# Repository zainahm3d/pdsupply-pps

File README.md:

# pdsupply-pps
single channel USB PD PPS capable power supply

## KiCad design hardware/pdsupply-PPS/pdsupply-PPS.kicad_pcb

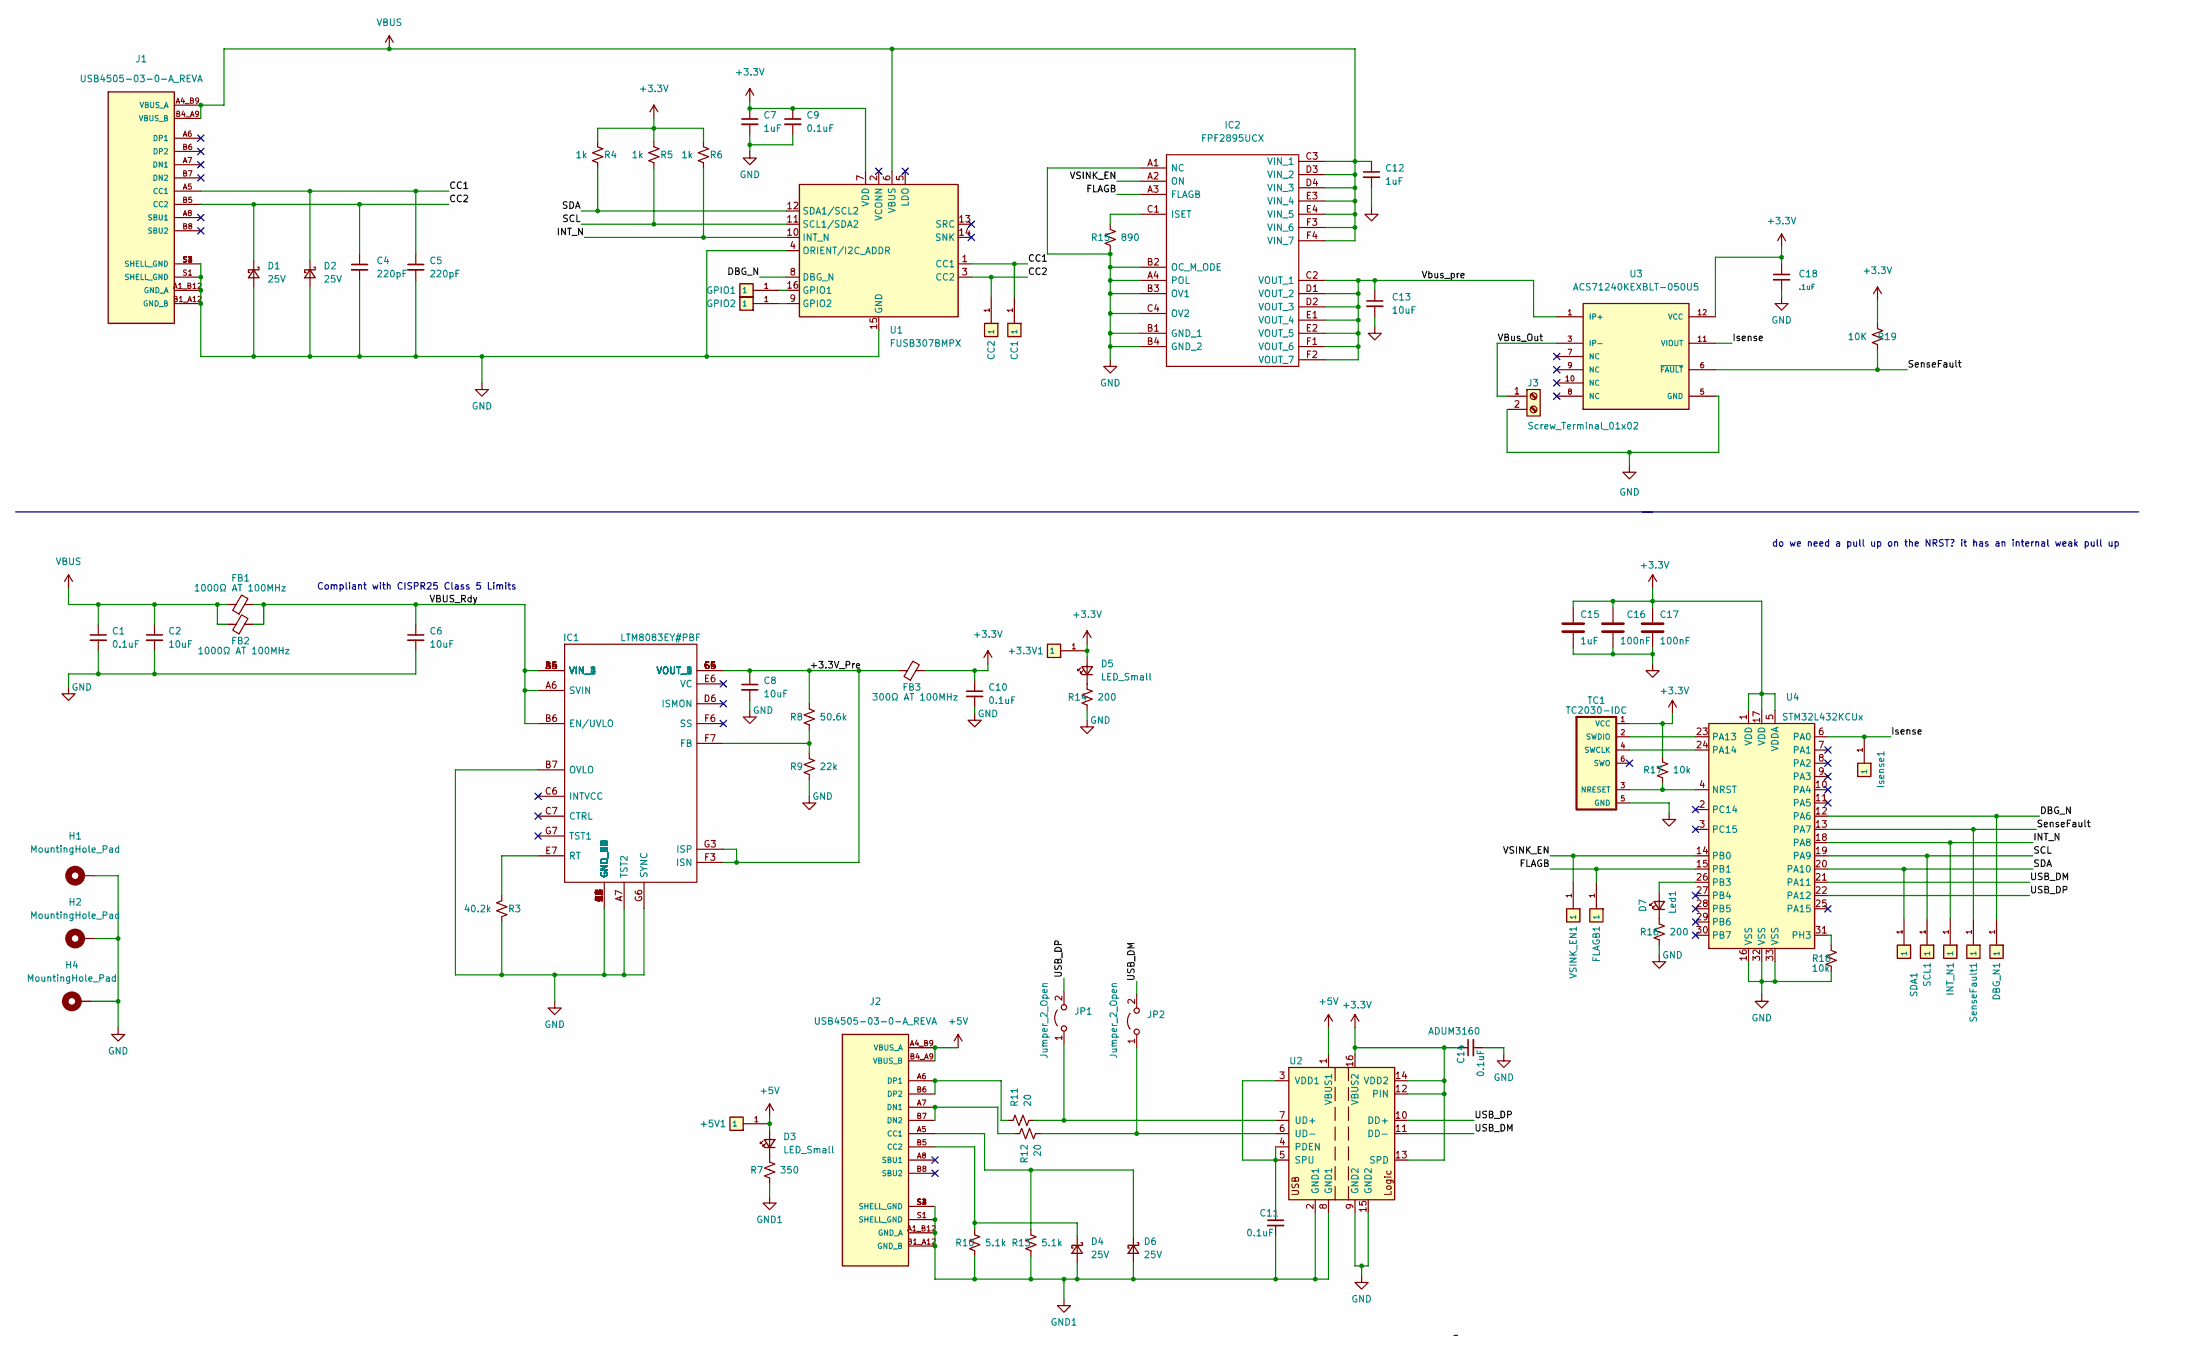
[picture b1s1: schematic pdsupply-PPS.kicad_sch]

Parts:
+3.3V1, +5V1: RCU-0C; TP+195X110; PARTREV BA1
C1, C9, C11, C14: 0.1uF; C_0603_1608Metric
C2, C6: 10uF; C_1206_3216Metric
C4, C5: 220pF; C_0603_1608Metric
C7, C12, C15: 1uF; C_0603_1608Metric
C8: 10uF; C_1210_3225Metric
C10: 0.1uF; C_0805_2012Metric
C13: 10uF; C_0603_1608Metric
C16, C17: 100nF; C_0603_1608Metric
C18: .1uF; C_0603_1608Metric
CC1, CC2: RCU-0C; TP+195X110; PARTREV BA1
D1, D2, D4, D6: 25V; D_0603_1608Metric
D3, D5: LED_Small; LED_0603_1608Metric
D7: Led1; LED_0603_1608Metric
DBG_N1: RCU-0C; TP+195X110; PARTREV BA1
FB1, FB2: 1000Ω AT 100MHz; L_0805_2012Metric
FB3: 300Ω AT 100MHz; L_0805_2012Metric
FLAGB1: RCU-0C; TP+195X110; PARTREV BA1
GPIO1, GPIO2: RCU-0C; TP+195X110; PARTREV BA1
H1, H2, H4: MountingHole_Pad; MountingHole_3mm_Pad
IC1: LTM8083EY#PBF; BGA49C80P7X7_625X625X242; Manufacturer_Part_Number LTM8083EY#PBF; Mouser Part Number 584-LTM8083EY#PBF
IC2: FPF2895UCX; BGA24C40P4X6_167X260X61; Manufacturer_Part_Number FPF2895UCX; Mouser Part Number 512-FPF2895UCX
INT_N1: RCU-0C; TP+195X110; PARTREV BA1
Isense1: RCU-0C; TP+195X110; PARTREV BA1
J1, J2: USB4505-03-0-A_REVA; GCT_USB4505-03-0-A_REVA; PARTREV A
J3: Screw_Terminal_01x02; TerminalBlock_Phoenix_MKDS-1,5-2_1x02_P5.00mm_Horizontal
JP1, JP2: Jumper_2_Open; SolderJumper-2_P1.3mm_Open_TrianglePad1.0x1.5mm
R3: 40.2k; R_0603_1608Metric
R4, R5, R6: 1k; R_0603_1608Metric
R7: 350; R_0603_1608Metric
R8: 50.6k; R_0603_1608Metric
R9: 22k; R_0603_1608Metric
R10, R13: 5.1k; R_0603_1608Metric
R11, R12: 20; R_0603_1608Metric
R14, R16: 200; R_0603_1608Metric
R15: 890; R_0603_1608Metric
R17, R18: 10k; R_0603_1608Metric
R19: 10K; R_0603_1608Metric
SCL1: RCU-0C; TP+195X110; PARTREV BA1
SDA1: RCU-0C; TP+195X110; PARTREV BA1
SenseFault1: RCU-0C; TP+195X110; PARTREV BA1
TC1: TC2030-IDC
U1: FUSB307BMPX; WQFN-16-1EP_3x3mm_P0.5mm_EP1.75x1.75mm
U2: ADUM3160; SOIC-16W_7.5x10.3mm_P1.27mm
U3: ACS71240KEXBLT-050U5; XDCR_ACS71240KEXBLT-050U5; PARTREV 3
U4: STM32L432KCUx; QFN-32-1EP_5x5mm_P0.5mm_EP3.45x3.45mm
VSINK_EN1: RCU-0C; TP+195X110; PARTREV BA1

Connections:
+3V3: +3.3V1.1, C7.1, C9.1, C10.1, C14.1, C15.1, C16.1, C17.1, C18.1, D5.2 (A), FB3.2, R4.2, R5.2, R6.2, R17.1, R19.2, TC1.1 (VCC), U1.7 (VDD), U2.12 (PIN), U2.13 (SPD), U2.14 (VDD2), U2.16 (VBUS2), U3.12 (VCC), U4.1 (VDD), U4.5 (VDDA), U4.17 (VDD)
+5V: +5V1.1, D3.2 (A), J2.A4_B9 (VBUS_A), J2.B4_A9 (VBUS_B), U2.1 (VBUS1)
/+3.3V_Pre: C8.1, FB3.1, IC1.F3 (ISN), IC1.F4 (VOUT_1), IC1.F5 (VOUT_2), IC1.G3 (ISP), IC1.G4 (VOUT_3), IC1.G5 (VOUT_4), R8.1
/CC1: C5.1, CC1.1, D2.1 (K), J1.A5 (CC1), U1.1 (CC1)
/CC2: C4.1, CC2.1, D1.1 (K), J1.B5 (CC2), U1.3 (CC2)
/DBG_N: DBG_N1.1, U1.8 (DBG_N), U4.12 (PA6)
/FLAGB: FLAGB1.1, IC2.A3 (FLAGB), U4.15 (PB1)
/INT_N: INT_N1.1, R6.1, U1.10 (INT_N), U4.18 (PA8)
/Isense: Isense1.1, U3.11 (VIOUT), U4.6 (PA0)
/SCL: R5.1, SCL1.1, U1.11 (SCL1/SDA2), U4.19 (PA9)
/SDA: R4.1, SDA1.1, U1.12 (SDA1/SCL2), U4.20 (PA10)
/SenseFault: R19.1, SenseFault1.1, U3.6 (~FAULT), U4.13 (PA7)
/USB_DM: JP2.2 (B), U2.11 (DD-), U4.21 (PA11)
/USB_DP: JP1.2 (B), U2.10 (DD+), U4.22 (PA12)
/VBUS_Rdy: C6.1, FB1.2, FB2.2, IC1.A4 (VIN_1), IC1.A5 (VIN_2), IC1.A6 (SVIN), IC1.B4 (VIN_3), IC1.B5 (VIN_4), IC1.B6 (EN/UVLO)
/VBus_Out: J3.1, U3.3 (IP-)
/VSINK_EN: IC2.A2 (ON), U4.14 (PB0), VSINK_EN1.1
/Vbus_pre: C13.1, IC2.C2 (VOUT_1), IC2.D1 (VOUT_2), IC2.D2 (VOUT_3), IC2.E1 (VOUT_4), IC2.E2 (VOUT_5), IC2.F1 (VOUT_6), IC2.F2 (VOUT_7), U3.1 (IP+)
GND: C1.2, C2.2, C4.2, C5.2, C6.2, C7.2, C8.2, C9.2, C10.2, C12.2, C13.2, C14.2, C15.2, C16.2, C17.2, C18.2, D1.2 (A), D2.2 (A), H1.1, H2.1, H4.1, IC1.A1 (GND_1), IC1.A2 (GND_2), IC1.A3 (GND_3), IC1.A7 (TST2), IC1.B1 (GND_4), IC1.B2 (GND_5), IC1.B3 (GND_6), IC1.B7 (OVLO), IC1.C1 (GND_7), IC1.C2 (GND_8), IC1.C3 (GND_9), IC1.C4 (GND_10), IC1.C5 (GND_11), IC1.D1 (GND_12), IC1.D2 (GND_13), IC1.D3 (GND_14), IC1.D4 (GND_15), IC1.D5 (GND_16), IC1.D7 (GND_17), IC1.E1 (GND_18), IC1.E2 (GND_19), IC1.E3 (GND_20), IC1.E4 (GND_21), IC1.E5 (GND_22), IC1.F1 (GND_23), IC1.F2 (GND_24), IC1.G1 (GND_25), IC1.G2 (GND_26), IC1.G6 (SYNC), IC2.A1 (NC), IC2.A4 (POL), IC2.B1 (GND_1), IC2.B2 (OC_M_ODE), IC2.B3 (OV1), IC2.B4 (GND_2), IC2.C4 (OV2), J1.A1_B12 (GND_A), J1.B1_A12 (GND_B), J1.S1 (SHELL_GND), J1.S2 (SHELL_GND), J1.S3 (SHELL_GND), J1.S4 (SHELL_GND), J3.2, R3.2, R9.2, R14.2, R15.2, R16.2, R18.2, TC1.5 (GND), U1.4 (ORIENT/I2C_ADDR), U1.15 (GND), U1.17 (GND), U2.9 (GND2), U2.15 (GND2), U3.5 (GND), U4.16 (VSS), U4.32 (VSS), U4.33 (VSS)
GND1: C11.2, D4.2 (A), D6.2 (A), J2.A1_B12 (GND_A), J2.B1_A12 (GND_B), J2.S1 (SHELL_GND), J2.S2 (SHELL_GND), J2.S3 (SHELL_GND), J2.S4 (SHELL_GND), R7.2, R10.2, R13.2, U2.2 (GND1), U2.8 (GND1)
unnamed: C11.1, U2.3 (VDD1), U2.4 (PDEN), U2.5 (SPU)
unnamed: D3.1 (K), R7.1
unnamed: D4.1 (K), J2.B5 (CC2), R10.1
unnamed: D5.1 (K), R14.1
unnamed: D6.1 (K), J2.A5 (CC1), R13.1
unnamed: D7.1 (K), R16.1
unnamed: D7.2 (A), U4.26 (PB3)
unnamed: GPIO1.1, U1.16 (GPIO1)
unnamed: GPIO2.1, U1.9 (GPIO2)
unnamed: IC1.E7 (RT), R3.1
unnamed: IC1.F7 (FB), R8.2, R9.1
unnamed: IC2.C1 (ISET), R15.1
unnamed: J2.A6 (DP1), J2.B6 (DP2), R11.1
unnamed: J2.A7 (DN1), J2.B7 (DN2), R12.2
unnamed: JP1.1 (A), R11.2, U2.7 (UD+)
unnamed: JP2.1 (A), R12.1, U2.6 (UD-)
unnamed: R17.2, TC1.3 (NRESET), U4.4 (NRST)
unnamed: R18.1, U4.31 (PH3)
unnamed: TC1.2 (SWDIO), U4.23 (PA13)
unnamed: TC1.4 (SWCLK), U4.24 (PA14)
VBUS: C1.1, C2.1, C12.1, FB1.1, FB2.1, IC2.C3 (VIN_1), IC2.D3 (VIN_2), IC2.D4 (VIN_3), IC2.E3 (VIN_4), IC2.E4 (VIN_5), IC2.F3 (VIN_6), IC2.F4 (VIN_7), J1.A4_B9 (VBUS_A), J1.B4_A9 (VBUS_B), U1.6 (VBUS)

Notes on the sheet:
Compliant with CISPR25 Class 5 Limits
do we need a pull up on the NRST? it has an internal weak pull up

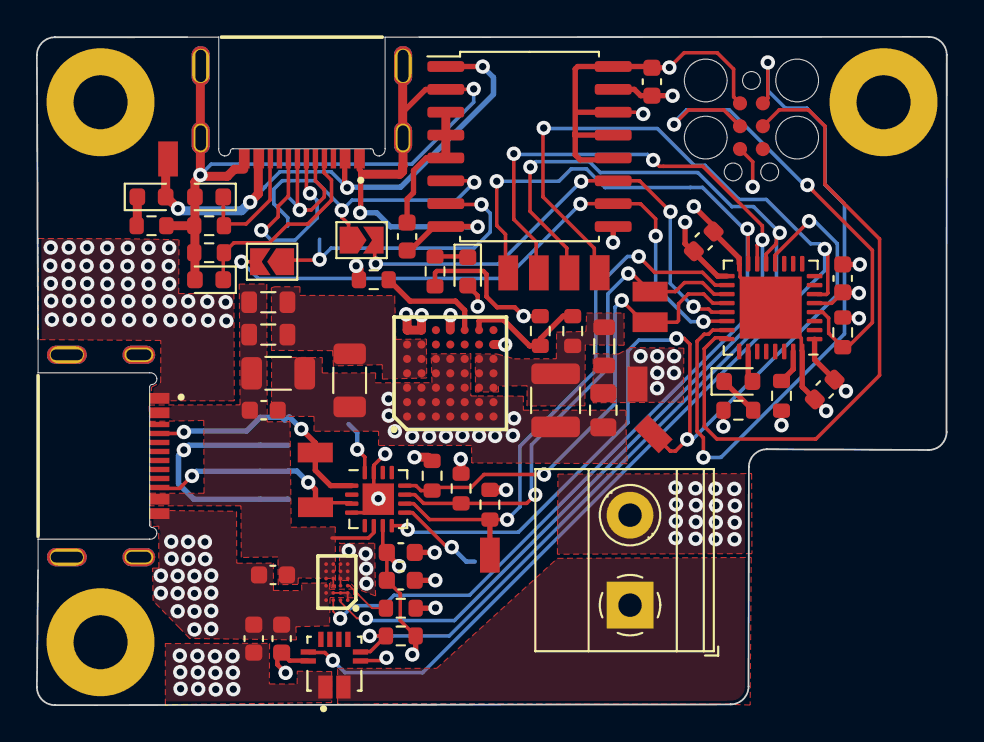
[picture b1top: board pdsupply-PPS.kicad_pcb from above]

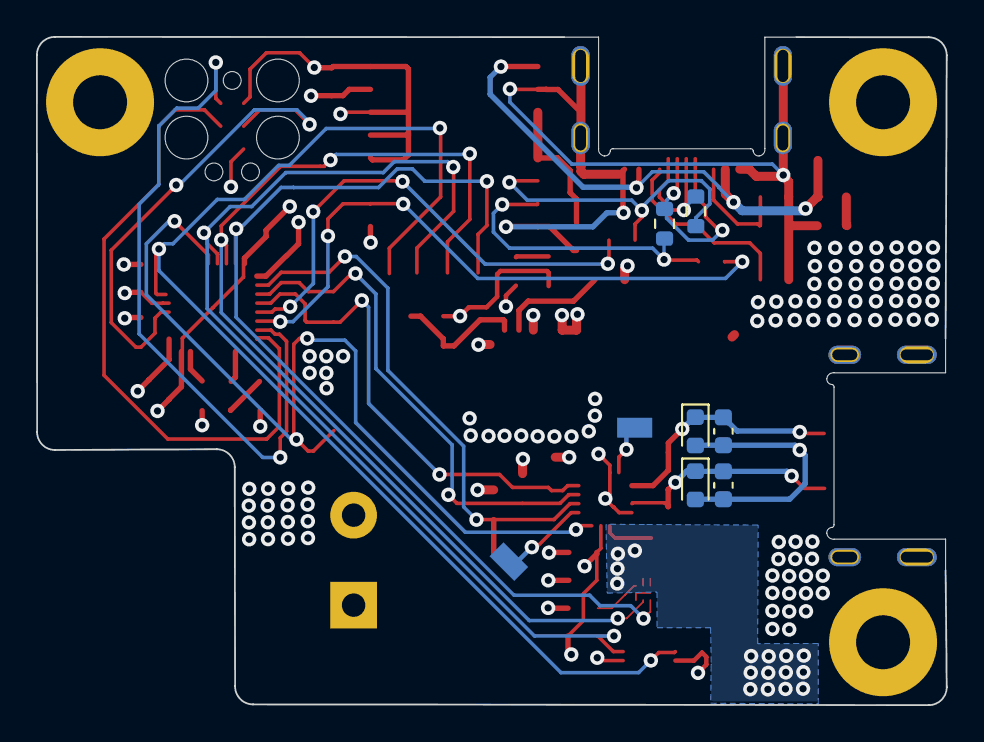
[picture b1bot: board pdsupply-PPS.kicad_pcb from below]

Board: 4 copper layers, 50.5 x 37.1 mm, 73 parts (8 on the bottom side), 41 nets.

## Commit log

2022-04-12 basic SCH done
2022-04-14 added a buck boost
2022-04-15 minor changes
2022-04-15 SCH 90% done
2022-04-17 cleaned up SCH
2022-04-21 SCH done
2022-04-27 Changed SW Conn
2022-05-16 FB assigned , started component placements
2022-05-17 component placement done
2022-06-05 started layout
2022-06-08 added few routes
2022-06-09 almost done with routing
2022-06-10 add initial GitHub actions ci config
2022-06-10 Include libopencm3
    wrote makefile
    basic gpio init and test
    Ozone jdebug file (not computer agnostic yet)
2022-06-10 almost done
2022-06-12 [WIP - UNTESTED] Scaffold out usb/uart comms
2022-06-13 added holes
2022-06-16 layout done!
2022-07-07 Removed ref Designators
2022-07-18 changed Pin A1 on FPF2895 to be connected to GND
2022-07-18 Version 1 schematic and PCB layout
2022-07-19 fixed DRC violations
